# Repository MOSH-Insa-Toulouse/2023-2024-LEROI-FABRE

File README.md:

# Projet MOSH
## Par Quentin et Laetitia 🥇
### ~~Le meilleur binôme~~ (il faut pas le dire) 

Cohésion d'équipe ☑️
## Diagramme du projet
```mermaid
graph TD;
    A[Capteur Graphite]-->B((Arduino Uno));
    F[Capteur Flex]-->B((Arduino Uno));
    G[Potentiomètre]-->B((Arduino Uno));
    B((Arduino Uno))-->D[Ecran LCD];
    B((Arduino Uno))-->C[Module Bluetooth];
    C[Module Bluetooth]-.->E[App Android];

```

<details>
<summary>  Etapes du projet MOSH :tada:  </summary>
  
  - [x] Attribution des inputs de l'arduino aux différents capteurs
  - [X] Electronique Analogique
  - [x] Schématique KiCad  
  - [x] Routage KiCad
  - [x] Impression du cricuit
  - [x] Percage
  - [X] Montage des capteurs sur le circuit imprimé (par Cathy, MERCIII)
  - [X] Code Arduino
  - [X] App Android
  - [X] Création du banc de test
  - [X] Création de la datasheet
        
</details>

# Quel est ce projet ?

Ce projet consiste en...

<details>
<summary> la création d'un capteur Graphite. </summary>
Un capteur graphite, c'est tout simplement un morceau de papier où l'on colorie une zone à l'aide d'un crayon à papier. Il permet de mesurer des variations de résistance lorqu'on le déforme. Voici la forme de capteur que nous utilisons : 

</details>

<details>
<summary> la création d'un shield Arduino. </summary>
Cela permet d'effectuer les acquisitions des données envoyées par notre capteur (des variations de tensions que nous pouvons traduire en résistance !). 
Nous y implémenterons également un capteur Flex dont voici la datasheet : (insérer la datasheet), un écran LCD pour afficher les données du capteur graphite ou du capteur flex, un potentiomètre qui permettra à l'utilisateur de naviguer dans un menu qui permet d'afficher les données du capteur graphite ou du capteur flex, un potentiomètre numérique qui permettra d'ajuster une résistance pour la maniulation des données du capteur graphite,... 

Pour cela, il nous faut créer le shield sous KiCad, le faire imprimer, percer le trous, et y monter nos capteurs.
</details>

<details>
<summary> la création d'un code Arduino. </summary>
Le code permettra de commander le microcontrôleur Arduino Uno : gestion des données, commnication Bluetooth (voir App android), choix de la résistance du potentiomètre numérique, affichage sur l'écran LCD...
</details>

<details>
<summary> la création d'une App Android. </summary>
Notre projet s'accompagne également d'une App Android : grâce à la communication Bluetooth, nous pouvons afficher sur un smartphone des graphiques des données enregistrées par nos deux capteurs. Nous créons l'app sur  MIT app Inventor (https://community.appinventor.mit.edu/).
</details>

<details>
<summary> tout ça pour l'élaboration d'une Datasheet ! </summary>
L'objectif final, le graal du projet, c'est de rédiger une datasheet du capteur Graphite. Le banc de test et notre code arduino nous ont permis de réaliser toutes les mesures. 
</details>

# Je veux aller voir...
 __(cliquez)__ 

## L'Electronique Analogique  [Clique](https://github.com/MOSH-Insa-Toulouse/2023-2024-LEROI-FABRE/tree/main/LTSpice%20-%20Electronique%20Analogique)
<details>
<summary> Explications. </summary>
    
Vous trouverez dans ce dossier le circuit analogique du capteur graphite. Il y a un amplificateur transimpédance et un filtre qui permettent d'obtenir un signal utilisable. En effet, le signal délivré par le capteur sans ce circuit est trop faible : il a un courant moyen de 100nA, donc il faudrait un microcontrôleur très précis pour pouvoir détecter des variations sur ce signal. C'est pourquoi nous l'amplifions. 

Les filtres sont nécessaires afin d'élminer les fréquences 50Hz dans lesquelles nos environnements sont baignés (à cause du réseau électrique), et d'autres fréquences parasites.

Voici un schéma, qui est une capture d'écran de nos simulations LTSpice : 

Les parties qui servent à filtrer sont dans les rectangles :
- le rectangle vert, avec une capacité de 100n, sert à filtrer le signal d'entrée. C'est un filtre passe-bas. Sa fréquence de transition est d'envirion 159Hz (formule f=1/(2*pi*R*C)). Il permet donc d'éliminer le bruit qui pourrait naître à l'entrée du circuit.
- le rectangle violet a une fonction similaire : c'est un filtre passe-bas, qui permet de filtrer le bruit en sortie, de fréquence de transition de 1591Hz.
- le rectangle rouge entoure le filtre passe-bas qui permet de filtrer le bruit environnant à 50Hz.

Le reste du circuit permet de réaliser l'amplifictation du signal. 

</details>

## Le KiCad ! [C'est ici](https://github.com/MOSH-Insa-Toulouse/2023-2024-LEROI-FABRE/tree/main/KiCad)

<details>
<summary> Explications. </summary>
    
Nous avons créé des empreintes KiCad pour notre capteur graphite, et pour les éléments qui ne sont pas déjà disponibles dans a librairie intégrée KiCad. Vous pouvez les retrouver dans le dossier KiCad. 

Nous avons ces contraintes pour la fabrication de nos shields : 
- largeur de routage de 0.5mm minimum.
- largeur de 0.5mm minimum entre différents routages afin d'assurer l'isolation électrique.
- nous avons élargi les pads du module bluetooth, de l'encodeur rotatoire, de l'écran OLED et des connecteurs du header à 2*2.54 (oval).
- vias de 0.8mm, cercle de 2.54mm.

Cela assure le fonctionnement du shield, et nous permet de percer les vias facilement.

| :exclamation:  ATTENTION CHERS COLLEGUES   |
|----------------------------------------------|

Nous avons commis des erreurs sur le fichier KiCad ! Chers ingénieurs/techniciens/instrumentateurs qui réalisez ce projet en suivant nos pas, n'oubliez pas de relier le MCP au reste du circuit !! Et n'inversez pas les pattes du LTC !!

</details>

## Non, je veux voir le code Arduino [Juste là](https://github.com/MOSH-Insa-Toulouse/2023-2024-LEROI-FABRE/tree/main/Arduino%20V2/projet_capteur) 

<details>
<summary> Explications. </summary>

Ce code a toutes ces fonctionalités :
- gère l'affichage sur l'écran OLED via une fonction.
- l'interruption DoEncodeur est réalisée à chaque fois que quelqu'un tourne l'encodeur rotatoire : l'utilisateur tourne l'encodeur, et au prochain tick de clock, linterruption sera réalisée. Elle permet d'ajouter +1 à la valeur que compte l'encodeur. Celui-ci sert à gérer le menu de l'écran OLED. Le principe est que lorsque nous tournons l'encodeur, c'est pour changer l'affichage de l'écran. Ainsi, si la valeur comptée par l'encodeur est paire nous aurons un afichage (capteur Flex), et s'il est impair, nous aurons un autre affichage (capteur graphite).
- la communication Bluetooth : nosu envoyons les données du capteur graphite ou du capteur flex à une application MIT via bluetooth. Si le module bluetooth recoit 1 de la part de l'application, c'est que l'utilisateur a appuyé sur le bouton "capteur flex". S'il recoit 2, c'est que l'utilisateur a appuyé sur "capteur graphite" dans l'app.
- la modification de la résistance du potentiomètre numérique : cela permet de calibrer le signal renvoyé par le capteur graphite.

  </details>

## Je préfère voir l'app Android [Okay...](https://github.com/MOSH-Insa-Toulouse/2023-2024-LEROI-FABRE/tree/main/App%20Android)
<details>
<summary> Explications. </summary>

Le projet s'accompagne d'une App qui fonctionne sur les téléphones android. Elle permet d'abotenir en temps réel les mesures du capteur graphite ou du capteur flex. Cela fonctionne grâce à une connexion Bluetooth. L'application est simple d'utilisation pour l'utilisateur.

Le code de l'application se fait sous [MIT App Inventor.](https://community.appinventor.mit.edu/) C'est un site gratuit simple dutilisation. Le code se fait via des blocks que l'utilisateur ajoute petit à petite, c'est très intuitif.
Voici une photo de l'application en fonctionnement :

</details>

## La Datasheet [Elle est au chaud ici](https://github.com/MOSH-Insa-Toulouse/2023-2024-LEROI-FABRE/tree/main/Datasheet)

## Des photos du projet, plutôt ! 📷 
<details>
<summary> Attention, époustouflant. </summary>

| :boom: BANG               |
|:----------------------------|
| Le capteur fonctionne ! On capte bien des variations quand on bouge le capteur Graphite |

| :boom: BANG               |
|:----------------------------|
| Le projet, c'est aussi beaucoup de fils lors de la phase de tests ! On a nettoyé tous ces fils ensuite, et c'était tout de suite beaucoup plus clair..! |

| :boom: BANG               |
|:----------------------------|
| Une des erreurs du fichier KiCad... |

| :boom: BANG               |
|:----------------------------|
| N'oubliez pas de faire un poisson d'avril à votre binôme |

| :boom: BANG               |
|:----------------------------|
| Quelle belle application Android |

| :boom: BANG               |
|:----------------------------|
| Petit selfie de fin de projet |

| :boom: BANG               |
|:----------------------------|
| C'était un projet à en tomber par terre |

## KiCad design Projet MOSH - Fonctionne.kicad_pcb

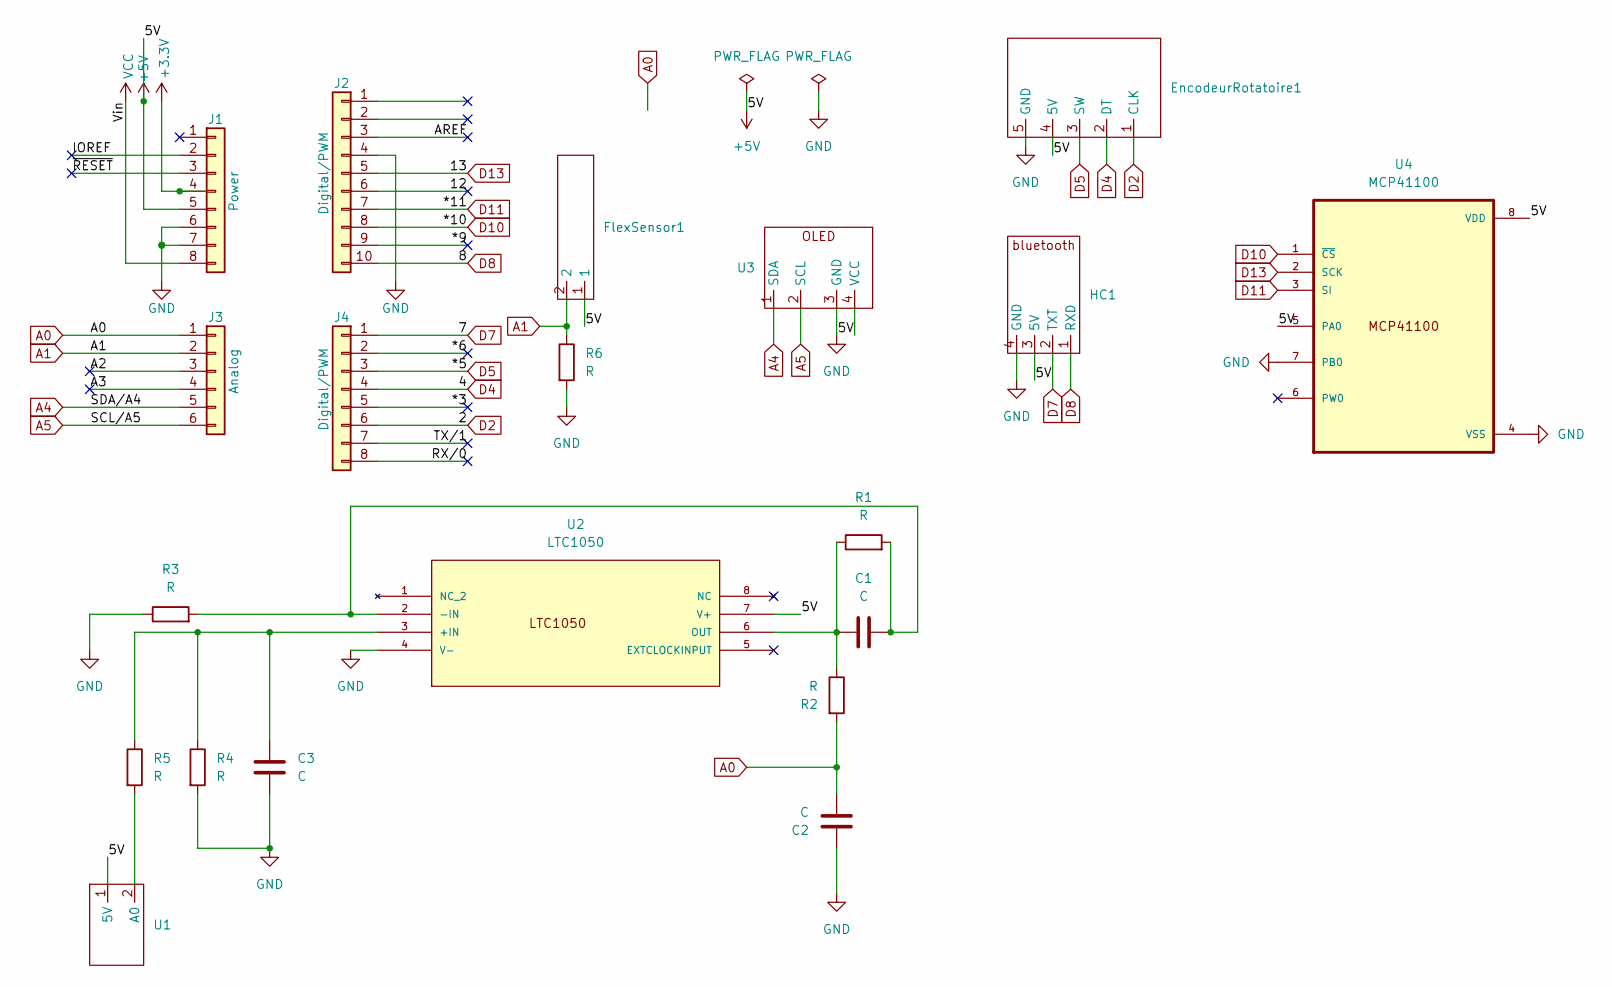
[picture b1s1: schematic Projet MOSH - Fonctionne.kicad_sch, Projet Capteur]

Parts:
C1: C; Capa rouge
C2, C3: C; Capa jaune
EncodeurRotatoire1: KY-040
FlexSensor1: Capteur FLEX
HC1: Bluetooth HC-05
J1: Power; PinSocket_1x08_P2.54mm_Vertical
J2: Digital/PWM; PinSocket_1x10_P2.54mm_Vertical
J3: Analog; PinSocket_1x06_P2.54mm_Vertical
J4: Digital/PWM; PinSocket_1x08_P2.54mm_Vertical
R1, R2, R3, R4, R5, R6: R; R 65 2
U1: capteur graphite
U2: LTC1050; LTC1050 et MCP; MANUFACTURER_PART_NUMBER ltc1050hs8
U3: OLED SCREEN
U4: MCP41100; LTC1050 et MCP

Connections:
+3V3: J1.4
+5V: EncodeurRotatoire1.4 (5V), FlexSensor1.1, HC1.3 (5V), J1.5, U1.1 (5V), U2.7 (V+), U3.4 (VCC), U4.5 (PA0), U4.8 (VDD)
/12: J2.6
/*3: J4.5
/*6: J4.2
/*9: J2.9
/A2: J3.3
/A3: J3.4
/AREF: J2.3
/IOREF: J1.2
/RX/0: J4.8
/TX/1: J4.7
/~RESET: J1.3
A0: C2.2, J3.1, R2.2
A1: FlexSensor1.2, J3.2, R6.1
A4: J3.5, U3.1 (SDA)
A5: J3.6, U3.2 (SCL)
D2: EncodeurRotatoire1.1 (CLK), J4.6
D4: EncodeurRotatoire1.2 (DT), J4.4
D5: EncodeurRotatoire1.3 (SW), J4.3
D7: HC1.2 (TXT), J4.1
D8: HC1.1 (RXD), J2.10
D10: J2.8, U4.1 (~CS)
D11: J2.7, U4.3 (SI)
D13: J2.5, U4.2 (SCK)
GND: C2.1, C3.2, EncodeurRotatoire1.5 (GND), HC1.4 (GND), J1.6, J1.7, J2.4, R3.1, R4.2, R6.2, U2.4 (V-), U3.3 (GND), U4.4 (VSS), U4.7 (PB0)
unnamed: R5.2, U1.2 (A0)
unnamed: C3.1, R4.1, R5.1, U2.3 (+IN)
unnamed: C1.2, R1.2, R3.2, U2.2 (-IN)
unnamed: C1.1, R1.1, R2.1, U2.6 (OUT)
VCC: J1.8

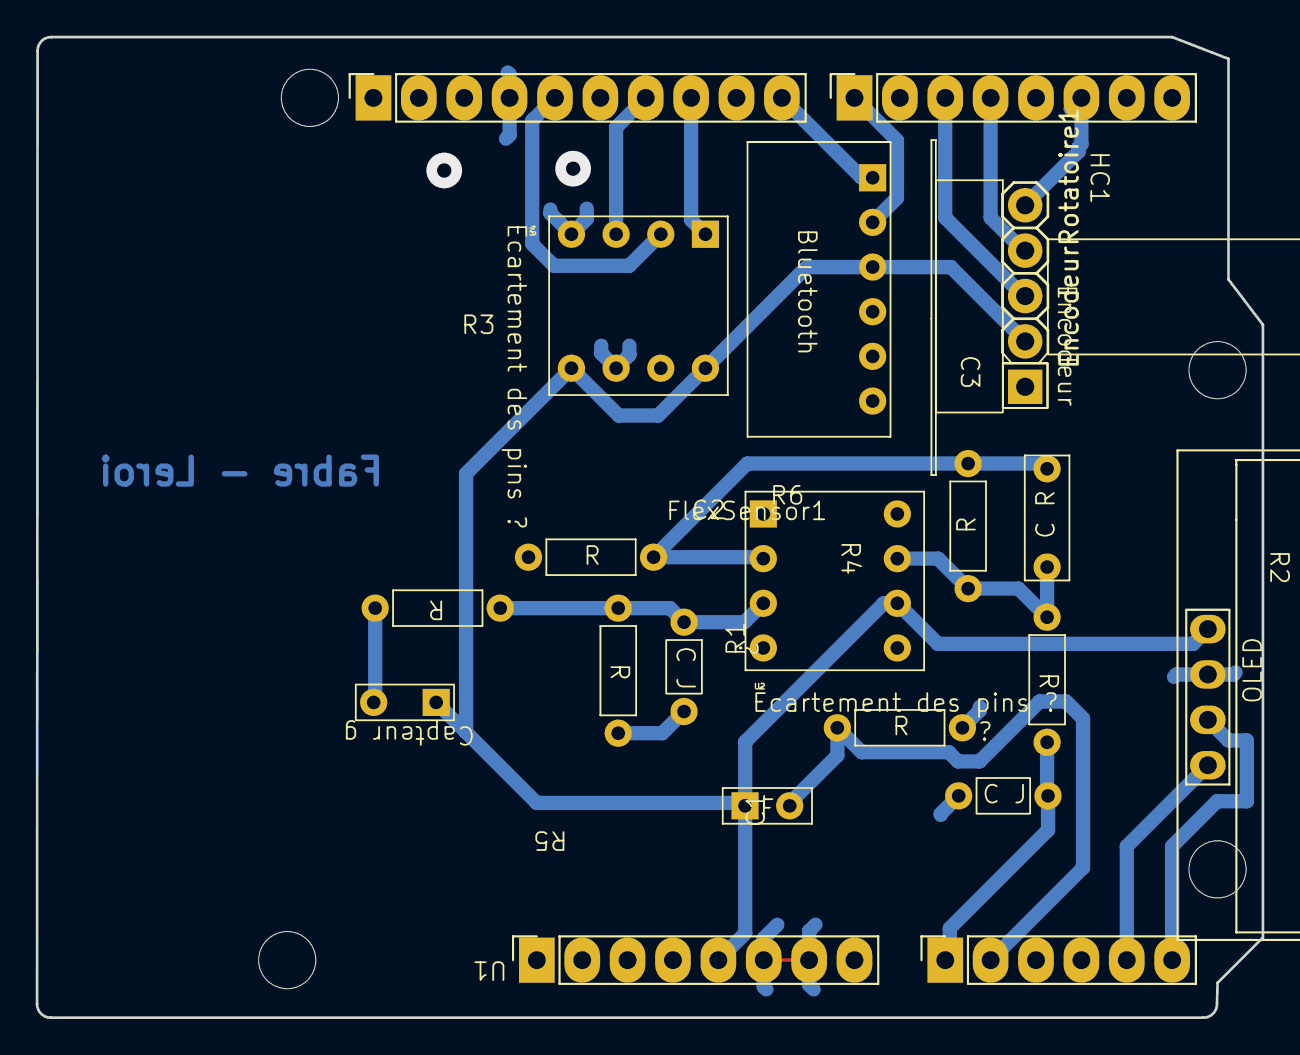
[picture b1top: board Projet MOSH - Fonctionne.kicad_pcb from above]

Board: 2 copper layers, 68.6 x 54.9 mm, 24 parts (0 on the bottom side), 18 nets.

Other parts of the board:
MH1, MH2, MH3, MH4: MountingHole_3.2mm

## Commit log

2024-03-11 Create KiCad
2024-03-11 Projet KiCad : démarrer le routage
2024-03-12 Add files via upload
    Début de routage
2024-03-13 Modification du PCB
2024-03-13 Fonctionne presque ! Juste deux zones GND à connecter et ce sera bon
2024-03-13 Create résistance.kicad_mod
    changement résistance
2024-03-18 maj 18 mars
2024-03-18 maj 2 18 mars : changements mineurs
2024-03-20 Wow
    It is workiiiiiing
2024-03-20 Changements
2024-03-20 Il manque a relier les vias
2024-03-25 Programme mis à jour le 25 mars
2024-03-26 Graph ok et Connexion BT OK, mais pas encore d'affichage des données par BT
2024-04-02 Final
2024-04-18 Photo page de garde
2024-04-18 Ajout image page de garde
2024-04-18 Ré organisation
2024-04-18 Ajout App
2024-04-18 Simple ré organisation
2024-04-18 Simple organisation
2024-04-20 Check
2024-04-20 Bonne version du Code !
2024-04-20 Tout petit chgmt
2024-04-20 Ajout Code MIT App Inventor
2024-04-20 Modif Images
2024-04-20 Arrangement dossiers
2024-04-22 Code avec fonctions calibrage
2024-04-23 Arduino, encore voir les pics avant d'avoir des mesures
2024-05-07 Finished code and results
2024-05-22 Excel
2024-05-29 Rename Sans titre.png to LTSpice
2024-05-29 Rename IMG_8603.HEIC to App+circuit
2024-05-29 Résultats terminés
2024-05-29 Datasheet
